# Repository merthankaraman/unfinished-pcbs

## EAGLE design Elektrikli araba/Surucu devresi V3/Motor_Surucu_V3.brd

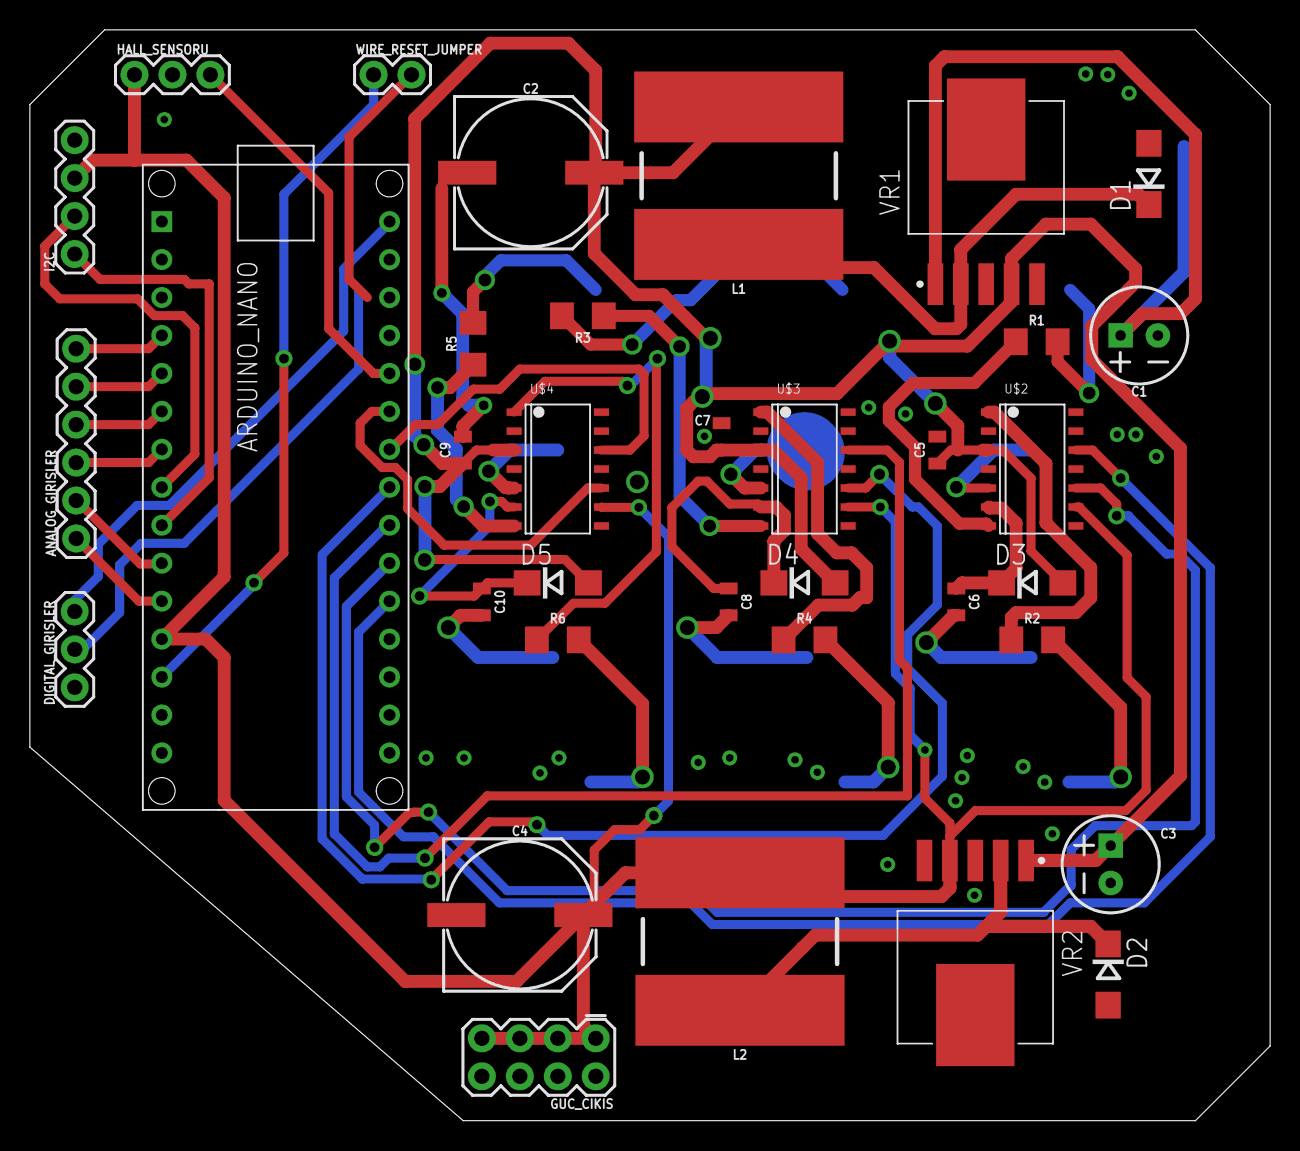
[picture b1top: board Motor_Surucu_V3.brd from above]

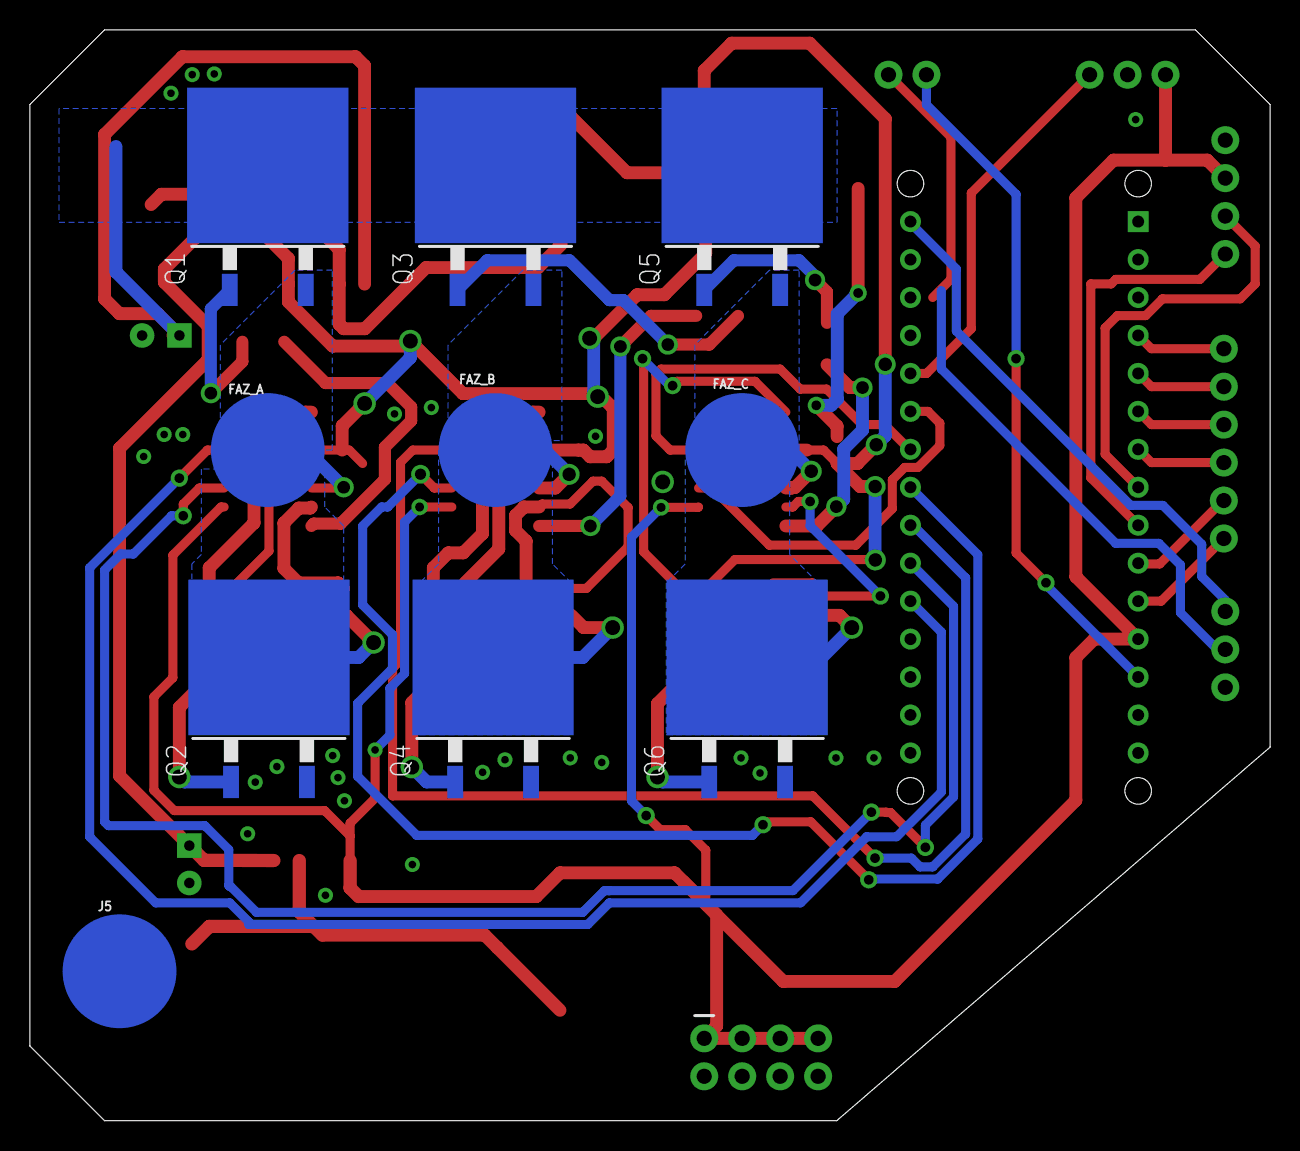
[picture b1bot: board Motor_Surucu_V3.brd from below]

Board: 2 copper layers, 83.0 x 73.0 mm, 45 parts (10 on the bottom side), 42 nets.

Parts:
ANALOG_GIRISLER: 1X06
C1, C3: 100uF; CPOL-RADIAL-2.5MM-6.5MM
C2, C4: 1mF/1000uF; PANASONIC_G
C5, C7, C9: 10µF 805; 0805
C6, C8, C10: 2.2µF 805; 0805
D1, D2, D3, D4, D5: SX34 3A 40V; DO214AC
DIGITAL_GIRISLER: 1X03
FAZ_A: SNAP-MALE
FAZ_B: SNAP-MALE
FAZ_C: SNAP-MALE
GUC_CIKIS: 2X4
HALL_SENSORU: 1X03
I2C: 1X04
J5: SNAP-MALE
L1, L2: 100uH 12X12 3.2A; INDUCTOR_SDR1307
Q1, Q2, Q3, Q4, Q5, Q6: CSD18542KTT; TO263-3
R1, R2, R3, R4, R5, R6: 100ohm 1206; 1206
U$1: ARDUINO_NANO
U$2, U$3, U$4: IR2113SMD; SOIC-14
VR1: LM2576HVS 12V; TO170P1435X465-6N
VR2: LM2576HVS 5V; TO170P1435X465-6N
WIRE_RESET_JUMPER: 1X02

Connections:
5V: C4.+, GUC_CIKIS.1, GUC_CIKIS.3, GUC_CIKIS.5, GUC_CIKIS.7, HALL_SENSORU.1, I2C.3, L2.P$2, U$1.5V, U$2.P$9, U$3.P$9, U$4.P$9, VR2.4
12V: C2.+, C3.1, C5.1, C7.1, C9.1, D3.A, D4.A, D5.A, L1.P$2, U$2.P$3, U$3.P$3, U$4.P$3, VR1.4, VR2.1
A2: ANALOG_GIRISLER.4, U$1.A2
A3: ANALOG_GIRISLER.3, U$1.A3
A6: ANALOG_GIRISLER.2, U$1.A6
A7: ANALOG_GIRISLER.1, U$1.A7
ADUSUK: U$1.D2, U$2.P$12
AYUKSEK: U$1.D3, U$2.P$10
BDUSUK: U$1.D4, U$3.P$12
BYUKSEK: U$1.D5, U$3.P$10
CDUSUK: U$1.D6, U$4.P$12
CYUKSEK: U$1.D7, U$4.P$10
FAZ_A: C6.2, FAZ_A.2, Q1.3, Q2.TAB, U$2.P$5
FAZ_B: C8.2, FAZ_B.2, Q3.3, Q4.TAB, U$3.P$5
FAZ_C: C10.2, FAZ_C.2, Q5.3, Q6.TAB, U$4.P$5
FREN_PIN: ANALOG_GIRISLER.5, U$1.A1
GAZ_PIN: ANALOG_GIRISLER.6, U$1.A0
GND: C1.2, C2.-, C3.2, C4.-, C5.2, C7.2, C9.2, D1.A, D2.A, DIGITAL_GIRISLER.1, GUC_CIKIS.2, GUC_CIKIS.4, GUC_CIKIS.6, GUC_CIKIS.8, HALL_SENSORU.2, I2C.4, J5.2, Q2.3, Q4.3, Q6.3, U$1.GND@1, U$1.GND@2, U$2.P$2, U$2.P$11, U$2.P$13, U$3.P$2, U$3.P$11, U$3.P$13, U$4.P$2, U$4.P$11, U$4.P$13, VR1.3, VR1.5, VR2.3, VR2.5
unnamed: D2.C, L2.P$1, VR2.2
unnamed: Q1.1, R1.2
unnamed: Q3.1, R3.2
unnamed: C6.1, D3.C, U$2.P$6
unnamed: R5.1, U$4.P$7
unnamed: R1.1, U$2.P$7
unnamed: Q2.1, R2.2
unnamed: R2.1, U$2.P$1
unnamed: C8.1, D4.C, U$3.P$6
unnamed: R3.1, U$3.P$7
unnamed: Q5.1, R5.2
unnamed: Q4.1, R4.2
unnamed: R4.1, U$3.P$1
unnamed: C10.1, D5.C, U$4.P$6
unnamed: Q6.1, R6.2
unnamed: R6.1, U$4.P$1
unnamed: D1.C, L1.P$1, VR1.2
RESET: U$1.RST@1, WIRE_RESET_JUMPER.1
SCL: I2C.1, U$1.A5
SDA: I2C.2, U$1.A4
SENSOR: HALL_SENSORU.3, U$1.D8
TORK_MODU: DIGITAL_GIRISLER.2, U$1.D10
VIN: C1.1, Q1.TAB, Q3.TAB, Q5.TAB, VR1.1
YON_PIN: DIGITAL_GIRISLER.3, U$1.D12

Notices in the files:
parts and their libraries:
SparkFun-Capacitors: Licensing: Creative Commons ShareAlike 4.0 International - https://creativecommons.org/licenses/by-sa/4.0
